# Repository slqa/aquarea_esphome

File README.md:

# Description
This project allows for controlling Aquarea F-series heat pumps directly from Home Assistant via standard ESPHome controls.
For it to function, special hardware is needed, which you will have to place between the remote control and the heat pump.
Thanks to this device, you are able to monitor heat pump states and issue your own commands.

```
  Heatpump RX ------|---|---/---------TX  REMOTE
           TX ------|   |   |         RX
            |       |   |   |         |
            |      RX  TX  RTS        |
            |      ESP12E             |
            |-------------------------|
```
I used hardware serial on pins GPIO15/GPIO13 and one pin for RTS from a GPIO5 Mini ESP board. In a 'normal' situation, the ESP12E only listens to communication between the remote and the heat pump, so you can have entity updates.
When you want to issue a state change from Home Assistant, the RTS pin is set, blocking communication from the remote to the heat pump. The ESP12E then sends the command and waits for confirmation.
After sending commands, it returns to the 'normal' state.
The Panasonic UART protocol has a baud_rate of 960, data_bits of 8, stop_bits of 1, parity of EVEN, and is inverted. My version of the bridge device realizes inversion at the hardware level, so there is no such setting in the YAML UART configuration.

Bridge PCB using ESP12E:

# How to use
Follow normal ESPHome steps
```bash
docker pull ghcr.io/esphome/esphome
docker run --rm -v "${PWD}":/config -it ghcr.io/esphome/esphome compile aquarea.yaml
docker run --rm -v "${PWD}":/config -it ghcr.io/esphome/esphome run aquarea.yaml
```

## 💾 Flashing Firmware via UART

Follow these steps to successfully flash your device's firmware using a UART adapter.

### 1. Wiring and Connection

Connect your **UART adapter** (or an ESP board with a USB level shifter) to the board's gold pin connector using the following pins:

| Pin | Function | Adapter Connection |
| :--- | :--- | :--- |
| **3.3V** | Power | Connect to **3.3V** on the adapter. |
| **TX** | Transmit | Connect to **RX** on the adapter. |
| **RX** | Receive | Connect to **TX** on the adapter. |
| **Gnd** | Ground | Connect to **Gnd** on the adapter. |

> ⚠️ **IMPORTANT:** If the PCB is still powered by the heat pump, **DO NOT CONNECT the 3.3V pin** from your adapter.

---

### 2. Entering Program Mode (Flash Mode)

To put the board into Flash Mode:

1.  **Short the PRG point:** Use a screwdriver or jumper wire to short the **PRG** test point (sometimes marked as old **SW1**).
2.  **Power Cycle:** While the **PRG** point is still shorted, quickly **power cycle** the PCB. You can do this by:
    * Disconnecting and immediately reconnecting the power **3.3V** pin.
    * Unplugging and replugging the main heat pump connector from the PCB.
    * Cycling the main power to the heat pump unit.
3.  **Release Short:** Once the power cycle is complete, **release the short** on the **PRG** point.

The device is now in **Flash Mode** and ready to accept new firmware.
# Home assistant entites

# Thank you
Many thanks for work done by<br>
https://github.com/v-s-c-o-p-e/geisha_aquarea_panasonic_arduino_esp8266_proxy
https://github.com/pemue-git/pcb/tree/master/WH-MDC05F3E5_comm

## Disclaimer of Liability

THIS SOFTWARE IS PROVIDED "AS IS", WITHOUT WARRANTY OF ANY KIND, EXPRESS OR IMPLIED, INCLUDING BUT NOT LIMITED TO THE WARRANTIES OF MERCHANTABILITY, FITNESS FOR A PARTICULAR PURPOSE AND NONINFRINGEMENT. IN NO EVENT SHALL THE AUTHORS OR COPYRIGHT HOLDERS BE LIABLE FOR ANY CLAIM, DAMAGES OR OTHER LIABILITY, WHETHER IN AN ACTION OF CONTRACT, TORT OR OTHERWISE, ARISING FROM, OUT OF OR IN CONNECTION WITH THE SOFTWARE OR THE USE OR OTHER DEALINGS IN THE SOFTWARE.

You are solely responsible for any damage to your property, data, or third-party devices that results from the use or misuse of this software. By using this software, you agree to assume all risks associated with its use.

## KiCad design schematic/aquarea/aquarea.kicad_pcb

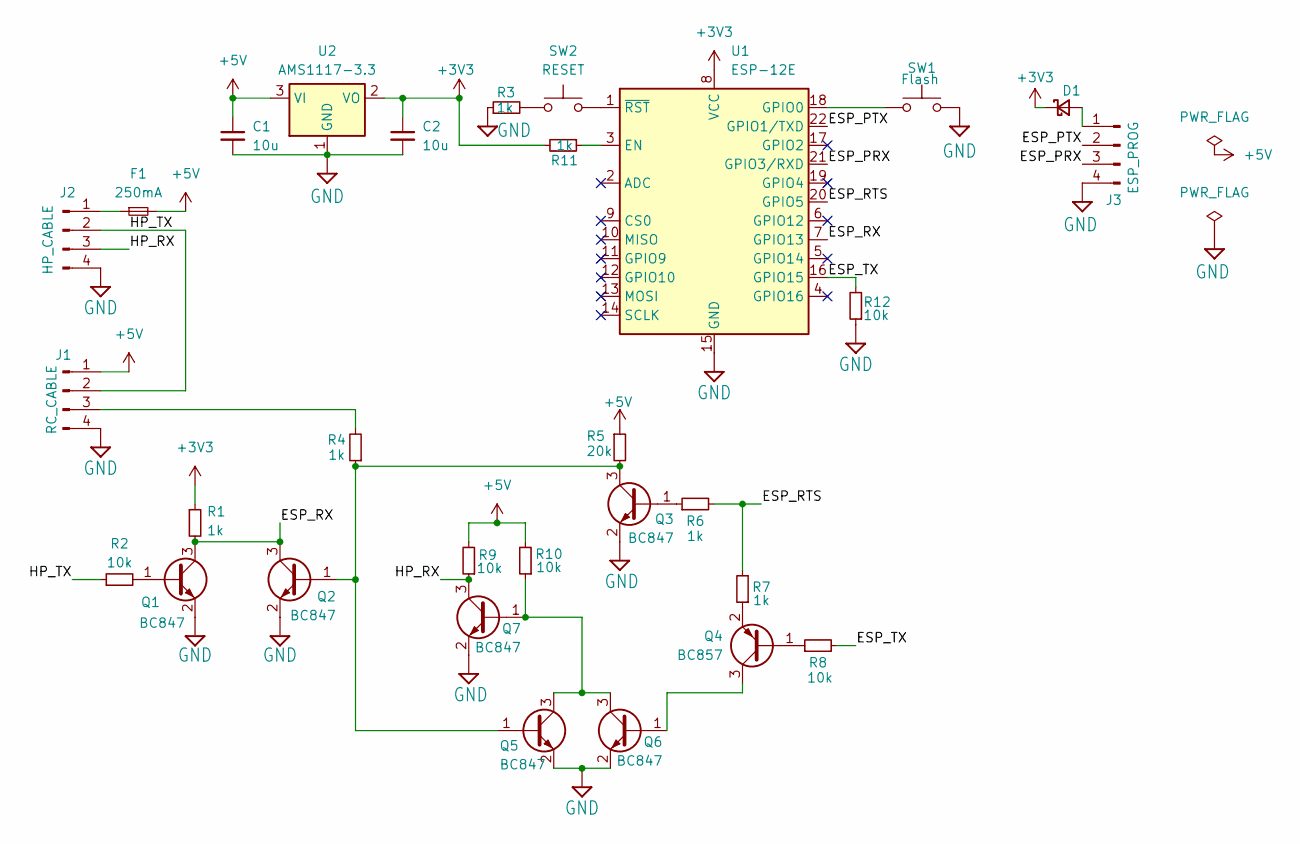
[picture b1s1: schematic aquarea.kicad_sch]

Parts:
C1, C2: 10u; CP_EIA-3216-10_Kemet-I_HandSolder
D1: D_Schottky_Small; D_MiniMELF_Handsoldering
F1: 250mA; Fuse_1812_4532Metric
J1: RC_CABLE; JST_XH_B4B-XH-A_1x04_P2.50mm_Vertical
J2: HP_CABLE; JST_XH_B4B-XH-A_1x04_P2.50mm_Vertical
J3: ESP_PROG; PinHeader_1x04_P2.54mm_Vertical
Q1, Q2, Q3, Q5, Q6, Q7: BC847; SOT-23
Q4: BC857; SOT-23
R1, R3, R4, R6, R7, R11: 1k; R_1206_3216Metric
R2, R8, R9, R10, R12: 10k; R_1206_3216Metric
R5: 20k; R_1206_3216Metric
SW1: Flash; R_0508_1220Metric
SW2: RESET; SW_Push_SPST_NO_Alps_SKRK
U1: ESP-12E
U2: AMS1117-3.3; SOT-223-3_TabPin2

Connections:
+3V3: C2.1, D1.1 (K), R1.1, R11.2, U1.8 (VCC), U2.2 (VO)
+5V: C1.1, F1.2, J1.1, R5.1, R9.2, R10.2, U2.3 (VI)
/ESP_PRX: J3.3, U1.21 (GPIO3/RXD)
/ESP_PTX: J3.2, U1.22 (GPIO1/TXD)
/ESP_RTS: R6.2, R7.2, U1.20 (GPIO5)
/ESP_RX: Q1.3 (C), Q2.3 (C), R1.2, U1.7 (GPIO13)
/ESP_TX: R8.2, R12.2, U1.16 (GPIO15)
/HP_RX: J2.3, Q7.3 (C), R9.1
/HP_TX: J1.2, J2.2, R2.1
GND: C1.2, C2.2, J1.4, J2.4, J3.4, Q1.2 (E), Q2.2 (E), Q3.2 (E), Q5.2 (E), Q6.2 (E), Q7.2 (E), R3.1, R12.1, SW1.2, U1.15 (GND), U2.1 (GND)
unnamed: D1.2 (A), J3.1
unnamed: J1.3, R4.2
unnamed: F1.1, J2.1
unnamed: Q1.1 (B), R2.2
unnamed: Q2.1 (B), Q3.3 (C), Q5.1 (B), R4.1, R5.2
unnamed: Q3.1 (B), R6.1
unnamed: Q4.1 (B), R8.1
unnamed: Q4.3 (C), Q6.1 (B)
unnamed: Q4.2 (E), R7.1
unnamed: Q5.3 (C), Q6.3 (C), Q7.1 (B), R10.1
unnamed: R3.2, SW2.1
unnamed: R11.1, U1.3 (EN)
unnamed: SW1.1, U1.18 (GPIO0)
unnamed: SW2.2, U1.1 (~RST)

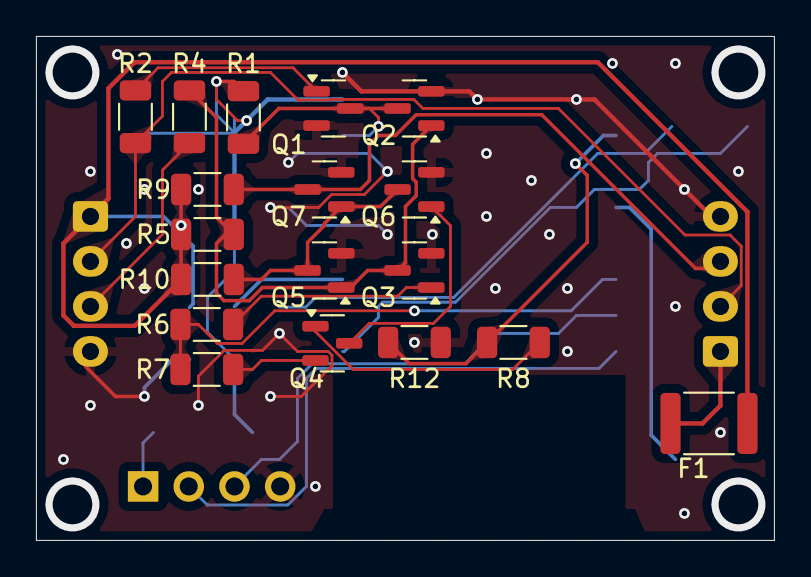
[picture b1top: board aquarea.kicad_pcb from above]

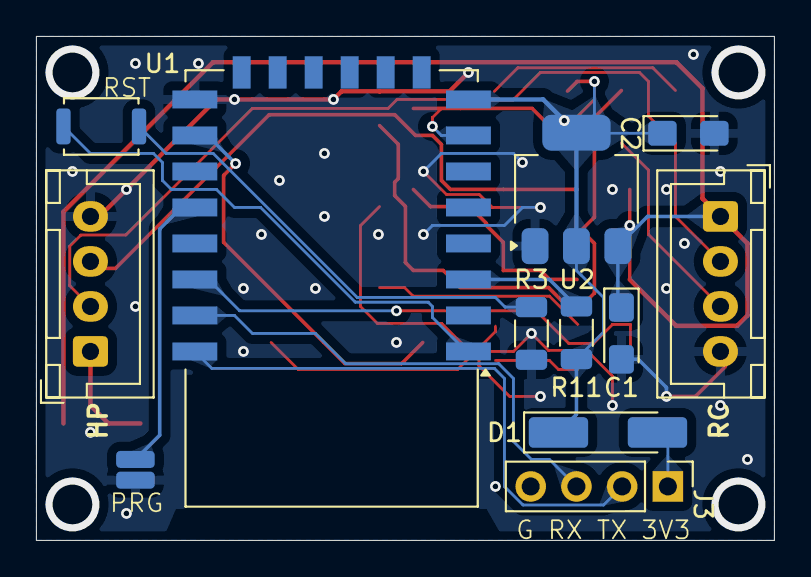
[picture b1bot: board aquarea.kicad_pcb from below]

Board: 2 copper layers, 41.0 x 28.0 mm, 30 parts (12 on the bottom side), 24 nets.

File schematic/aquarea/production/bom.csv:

Designator,Footprint,Quantity,Value,LCSC Part #
"C1, C2",CP_EIA-3216-10_Kemet-I_HandSolder,2,10u,
D1,D_MiniMELF_Handsoldering,1,D_Schottky_Small,
F1,1812,1,250mA,
J1,JST_XH_B4B-XH-A_1x04_P2.50mm_Vertical,1,RC_CABLE,
J2,JST_XH_B4B-XH-A_1x04_P2.50mm_Vertical,1,HP_CABLE,
J3,PinHeader_1x04_P2.54mm_Vertical,1,ESP_PROG,
"Q1, Q2, Q3, Q5, Q6, Q7",SOT-23,6,BC847,
Q4,SOT-23,1,BC857,
"R1, R11, R3, R4, R6, R7",1206,6,1k,
"R10, R12, R2, R8, R9",1206,5,10k,
R5,1206,1,20k,
SW1,0508,1,Flash,
SW2,SW_Push_SPST_NO_Alps_SKRK,1,RESET,
U1,ESP-12E,1,ESP-12E,
U2,SOT-223-3_TabPin2,1,AMS1117-3.3,

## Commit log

2025-07-11 Added images
2025-07-11 Fix typo in readme
2025-07-12 Fix config dummy entries
2025-07-18 Add brige schematic
2025-08-02 Schematic correction and readme update
2025-08-12 Add support for booster heater binary sensor
2025-09-05 Add aplha schematics for proxy device
2025-09-06 Enable setting initial values on startup
2025-09-06 Fix after merge
2025-09-13 Update schematic andpcb after tests; add bom and gerbers
2025-09-13 Update schematic
2025-09-13 Update svg
2025-10-13 Update README.md - uart flashing
2025-11-16 Add proper reset handling and optimize design adround antenna
2026-02-28 Set RTS pin mode to output in setup
2026-03-03 Fix pin_mode flag in setup method
